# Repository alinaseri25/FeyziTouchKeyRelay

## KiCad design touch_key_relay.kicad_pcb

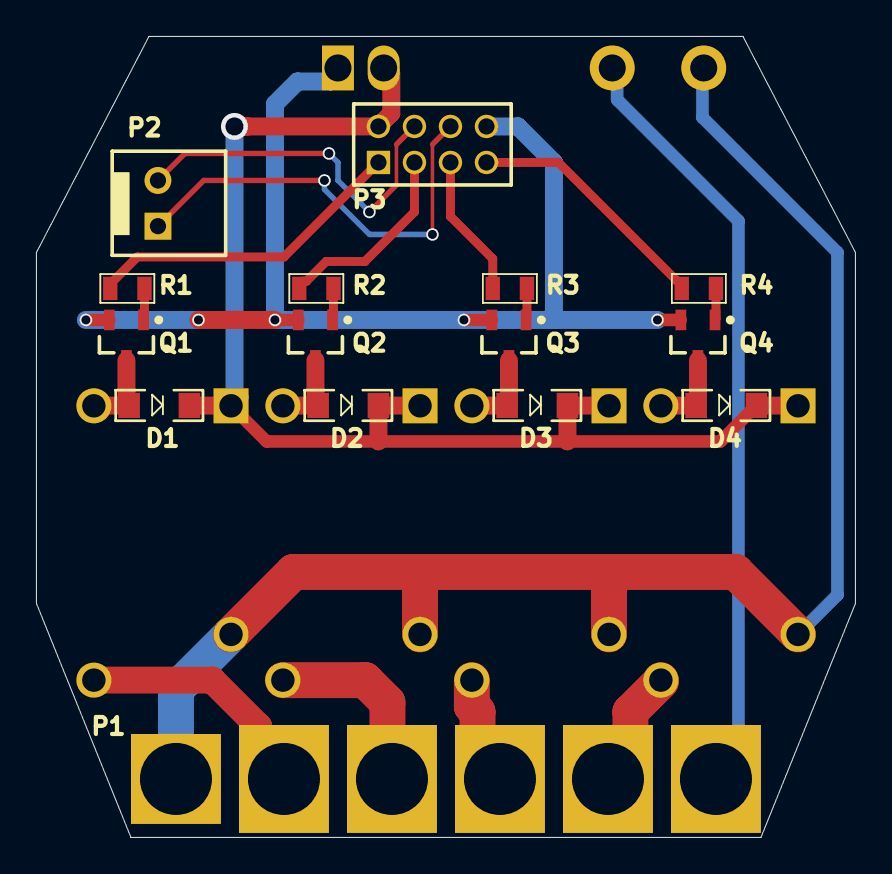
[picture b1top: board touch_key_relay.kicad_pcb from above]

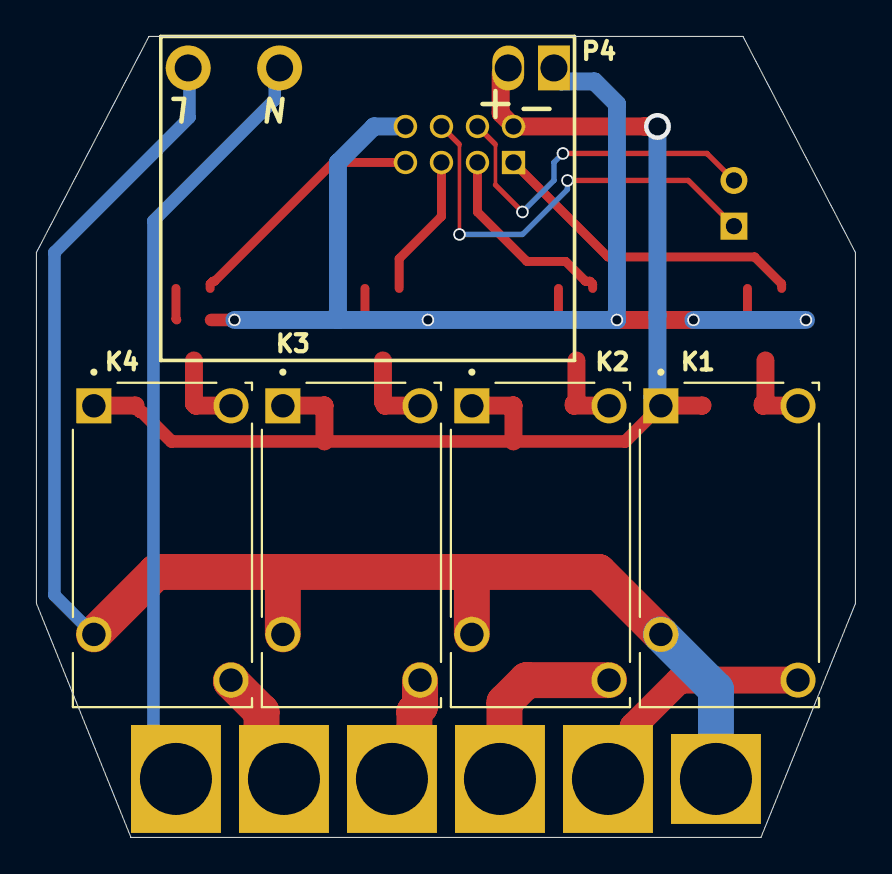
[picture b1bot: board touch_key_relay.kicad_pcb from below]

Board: 2 copper layers, 45.5 x 44.5 mm, 20 parts (5 on the bottom side), 22 nets.

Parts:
D1, D2, D3, D4: 1N4148_SMD; SOD-80
K1, K2, K3, K4: J0971CS5VDC.45; RELAY_J0971CS5VDC.45
P1: PTR6-R5.08; PTR6R-5.08
P2: SIG-2M; SIG2M
P3: HDR 2X4(2mm); HDR2*4(2mm)
P4: PTR4-R3.81; PTR4R-5.08
Q1, Q2, Q3, Q4: 2N3904; SOT23
R1, R2, R3, R4: 1K; RES 0805

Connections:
+5V: D1.2, D2.2, D3.2, D4.2, K1.A1, K2.A1, K3.A1, K4.A1, P3.2, P4.2
GND: P3.8, P4.1, Q1.2, Q2.2, Q3.2, Q4.2
L: P1.6, P4.3
L1: K1.14, P1.2
L2: K2.14, P1.3
L3: K3.14, P1.4
L4: K4.14, P1.5
N: K1.11, K2.11, K3.11, K4.11, P1.1, P4.4
NetD1_1: D1.1, K1.A2, Q1.3
NetD2_1: D2.1, K2.A2, Q2.3
NetD3_1: D3.1, K3.A2, Q3.3
NetD4_1: D4.1, K4.A2, Q4.3
NetQ1_1: Q1.1, R1.1
NetQ2_1: Q2.1, R2.1
NetQ3_1: Q3.1, R3.1
NetQ4_1: Q4.1, R4.1
RELAY_1: P3.1, R1.2
RELAY_2: P3.3, R2.2
RELAY_3: P3.5, R3.2
RELAY_4: P3.7, R4.2
RS485_N: P2.1, P3.6
RS485_P: P2.2, P3.4
